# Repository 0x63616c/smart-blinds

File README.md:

# Smart Blinds

Compact, rechargeable blind controllers for seven windows, with one spare.
White printed enclosures, USB-C charging, physical buttons and Home Assistant control.

**Current stage: prototype design.** This repository is being designed afresh. The inherited
USB-C boards below are references, not the new blind controller or a battery charger.
No complete unit has been built or physically validated.

[Current enclosure](docs/mechanical/enclosure-v2.md) · [Enclosure comparison](docs/mechanical/2026-10-19-holder-and-drive-trade-study.md) · [Electronics comparison](docs/electrical/2026-10-19-power-control-trade.md) ·
[Design brief](docs/brief.md) · [Progress](docs/status.md) · [Measurements](docs/measurements.json) ·
[Validation plan](docs/verification-plan.md) · [Shopping list](bom/README.md) · [Wi-Fi motion checkpoint](docs/firmware/wifi-motion.md) · [Local ownership](docs/firmware/local-ownership.md)

## The product

- One integrated controller and one 3S2P Samsung 50E battery pack per blind.
- PCB-mounted cell holders are being evaluated on a separate protected carrier to simplify assembly.
- Existing Recfountik JGB37-520 12 V / 111 RPM encoder motors.
- A small white enclosure mounted low on the wall, with accessible USB-C and up/down buttons.
- Group commands align the **physical bottom edges** of different-height blinds.
- A short remote-command preparation delay is acceptable; immediate local response is the target. Raw button STOP/wake is implemented; calibrated up/down gestures are still being completed.
- 60 days between charges is the design target; 90 days is a stretch, pending measured power use.
- Compare at least three enclosure layouts before choosing the packaging and PCB outline.
- Optimize the total cost for eight units, including JLCPCB assembly fees, packs, fixings and wiring.

The first milestone is a complete, costed design for **two prototypes**. Two different-height
blinds are needed to test synchronization before committing to the eight-unit batch.

## Design gallery

**Cleaner layout in progress:** the [54 × 80 mm controller](hw/routing/clean-main/)
is rebuilt from the current circuit source, with local footprints and all referenced models.
It has 206 gridded components, outward-facing connectors, rounded corners and sparse markings.
The [current review](docs/reviews/2026-10-21-clean-layout/source-driven-route.md)
records the geometry, library, ground-return and source checks.
**352 connections remain open**; this is a partial design, not a fabrication release.
The automatic gallery rebuilds the current route before rendering it. The smaller
196-part route is retained as a collapsed historical comparison.

These images are generated from the design sources. [Preview generation and provenance](docs/previews.md).
A green preview badge means the images generated successfully, not that the hardware is validated.
The [current 118 × 196 × 77 mm enclosure](docs/mechanical/enclosure-v2.md) has
an inward-facing controller, removable protected cassette and 22 installed
printed pieces. Its source-bound local review passes 17 nominal geometry checks;
physical motor/holder fit, strength and assembly remain untested. The current
assembly pictures use component envelopes; the KiCad view shows the populated board.
Older enclosure images retain their [known orientation error](docs/mechanical/pcb-orientation-review.md)
and are labelled historical. Fresh current-source images are published by CI.

<!-- previews:start -->
### Cleaner controller — current routing draft

Current 54 × 80 mm black four-layer controller draft, regenerated from the 206-part circuit capture. Grid placement, outward-facing connectors and the implemented USB-C, local supply and protection routes are checked on the saved filled board. 352 connections and three documented hybrid-footprint type findings remain; current, thermal, surge, RF and physical qualification are unfinished. Not a fabrication release.

[Source](hw/routing/clean-main/emit.py) · [Generated files](docs/generated/clean-controller-route/)

<details>
<summary>Historical enclosure — current exterior</summary>

Historical assembly checkpoint. Its PCB orientation and service geometry are superseded by the ongoing enclosure rework. 115 × 174 × 71 mm white enclosure candidate, with front buttons and underside USB-C. Buttons project to 72.2 mm. This compact version requires holder tails and solder joints trimmed to the documented limit; motor-family fit and printed tolerances remain provisional.

[Source](cad/source/compact_retained.scad) · [Generated files](docs/generated/compact-holder-closed/)

</details>

<details>
<summary>Historical removable battery cassette and compact drive</summary>

Historical assembly checkpoint. Its PCB orientation and service geometry are superseded by the ongoing enclosure rework. Two opposing three-cell carrier boards fit in a removable cassette. Separate controller supports, cable routes and adjustable front buttons are modeled. The controller is shown as a reserved volume; exact holder fastening and physical load tests remain open.

[Source](cad/source/compact_retained.scad) · [Generated files](docs/generated/compact-holder-assembly/)

</details>

<details>
<summary>Historical enclosure — service view</summary>

Historical assembly checkpoint. Its PCB orientation and service geometry are superseded by the ongoing enclosure rework. The cover and cassette lid are separated to show access. Two integral cleats and one mounting screw retain the cassette; its modeled release and removal paths clear the controller and drive. These are prototype-fit files, pending tolerance and load qualification.

[Source](cad/source/compact_retained.scad) · [Generated files](docs/generated/compact-holder-exploded/)

</details>

<details>
<summary>Current controller — source placement</summary>

Current 54 × 80 mm unrouted source capture: 206 components and 649 physical pin identities. The routing emitter applies three reviewed protection-part moves and the per-part model/silkscreen refinements. The larger routed draft appears above.

[Source](hw/layouts/blind-main/main-test/main-test.kicad_pcb) · [Generated files](docs/generated/main-controller-placement/)

</details>

<details>
<summary>Historical smaller controller — partial power routing</summary>

Historical 196-part, 54 × 68.5 mm route retained for comparison. Its 1013 segments, 255 vias and 122 open connections belong to the earlier circuit and placement. It is not the current controller or a fabrication release.

[Source](hw/routing/blind-main/main-routed.kicad_pcb) · [Generated files](docs/generated/main-power-route/)

</details>

<details>
<summary>Companion battery carrier — experimental copper</summary>

Two-layer companion carrier with 35 copper segments, 12 vias and no disconnected nets. Silkscreen and library comparisons pass; four mounting-hole courtyard findings remain. Experimental only: current capacity, holder loading, insulation and pack assembly still require qualification.

[Source](hw/routing/blind-pack-companion/companion-routed.kicad_pcb) · [Generated files](docs/generated/companion-routed/)

</details>

<details>
<summary>Primary battery carrier — connected routing study</summary>

Experimental 451-segment, 129-via route with all 35 nets physically connected and zero unconnected items. Eleven injected-fault checks cover current/Kelvin topology, protected-ground communication clamps and same-net solder-land clearance. Silkscreen and library comparisons pass. Four mounting-hole courtyard findings and thermal, transient, holder and assembly qualification remain. Not a fabrication release.

[Source](hw/routing/blind-pack-primary/primary-routed.kicad_pcb) · [Generated files](docs/generated/primary-current-route/)

</details>

<details>
<summary>Reusable battery-loading fixture</summary>

Reusable workshop supports for the wired carrier pair. The rear tray is fitted before turning the cassette; broad captive pads and temporary clamps support the modeled sequence. Eight printed tools are shared across all builds and add no installed parts. Cell retention, handling forces and pigtail restraint still require physical qualification.

[Source](cad/source/holder_pair_fixture.scad) · [Generated files](docs/generated/holder-pair-fixture/)

</details>

<details>
<summary>Battery loading with the rear tray fitted</summary>

The first cell row is enclosed by the rear tray before turning onto a supporting cradle to load the second row. Two temporary clamps use broad pads against the tray. This is a nominal geometric sequence, pending load and tolerance tests.

[Source](cad/source/holder_pair_fixture.scad) · [Generated files](docs/generated/holder-pair-tray/)

</details>

<details>
<summary>Captive pressure pad detail</summary>

A broad captive pad spreads the temporary clamp load; the screw tip remains clear of the tray in the nominal model. Retention and head-stop geometry are checked. Safe tightening force and print creep remain unqualified.

[Source](cad/source/holder_pair_fixture.scad) · [Generated files](docs/generated/holder-pair-pad/)

</details>

<details>
<summary>Complete controller schematic</summary>

Eleven native KiCad sheets cover all 206 circuit features and 649 physical pin identities. The exported net partition matches the current capture; seven documented ERC findings remain. No physical hardware has been powered.

[Source](hw/schematics/blind-main/smart-blinds-main.kicad_sch) · [Generated files](docs/generated/main-controller-schematic/) · [PDF](docs/generated/main-controller-schematic/schematic.pdf)

</details>

<details>
<summary>Historical enclosure — mechanism section</summary>

Historical assembly checkpoint. Its PCB orientation and service geometry are superseded by the ongoing enclosure rework. Two captive M2 adjusters set the plungers to first electrical closure at the 0.4 mm positive stop. Jam nuts lock the setting. Switch return, printed friction, adjustment and repeated operation still require physical tests.

[Source](cad/source/compact_retained.scad) · [Generated files](docs/generated/compact-holder-buttons/)

</details>

<details>
<summary>Historical enclosure — removable assembly</summary>

Historical assembly checkpoint. Its PCB orientation and service geometry are superseded by the ongoing enclosure rework. Six holders on opposing carrier boards, a separate insulating barrier and a removable printed shell. The assembled cassette releases with a 2.5 mm lift and then moves forward; disconnect and handle the cables separately.

[Source](cad/source/compact_retained.scad) · [Generated files](docs/generated/retained-cassette/)

</details>

<details>
<summary>Historical enclosure — cutaway</summary>

Historical assembly checkpoint. Its PCB orientation and service geometry are superseded by the ongoing enclosure rework. The cassette pocket captures the integral backplate cleat. Nominal interference confirms capture before the release slide; printed strength, creep and fit remain prototype tests.

[Source](cad/source/compact_retained.scad) · [Generated files](docs/generated/retained-cleat-section/)

</details>

<details>
<summary>Holder carrier enclosure — provisional exterior</summary>

Original 170 × 158 × 64 mm packaging study using six PCB-mounted holders and an independent chain shaft. Retention, electrical layout and purchased-part fit are still in development.

[Source](cad/source/packaging_v2.scad) · [Generated files](docs/generated/holder-closed/)

</details>

<details>
<summary>Battery holders and supported drives, at the same scale</summary>

Six packaging reservations. The two welded-pack options remain size references; the holder alternatives compare assembly effort, width and depth.

[Source](cad/parameters/packaging-v2.json) · [Generated files](docs/generated/holder-comparison/)

</details>

<details>
<summary>Protected carrier and supported drive — exploded study</summary>

Original 170 × 158 × 64 mm packaging study using six PCB-mounted holders and an independent chain shaft. Retention, electrical layout and purchased-part fit are still in development.

[Source](cad/source/packaging_v2.scad) · [Generated files](docs/generated/holder-exploded/)

</details>

<details>
<summary>One protected carrier — internal arrangement</summary>

Original 170 × 158 × 64 mm packaging study using six PCB-mounted holders and an independent chain shaft. Retention, electrical layout and purchased-part fit are still in development.

[Source](cad/source/packaging_v2.scad) · [Generated files](docs/generated/holder-inside/)

</details>

<details>
<summary>Motor driver — native KiCad circuit study</summary>

Fourteen components and 43 physical pin connections agree with the atopile board graph. This open block has four documented ERC boundary findings; supply, controller, motor connector and regenerative-energy clamp are not yet integrated.

[Source](hw/schematics/blind-controller/motor-test.kicad_sch) · [Generated files](docs/generated/motor-schematic/)

</details>

<details>
<summary>Motor cutoff and reset — native KiCad circuit study</summary>

Four ICs and ten passive parts. All 49 physical pin connections checked against the compiled circuit; two explicit external-power ERC findings. Physical cutoff and full-board qualification remain open.

[Source](hw/schematics/blind-supervisor/supervisor-test.kicad_sch) · [Generated files](docs/generated/supervisor-schematic/)

</details>

<details>
<summary>USB-C-fed 3S charger — native KiCad circuit study</summary>

36-part capture with 101 physical pins checked. A fourth PMID capacitor follows DC-bias review; effective capacitance remains a curve-based planning estimate. Ten explicit ERC findings and unfinished power/pack integration. Not a charging or fabrication release.

[Source](hw/schematics/blind-charger/charger-test.kicad_sch) · [Generated files](docs/generated/charger-schematic/)

</details>

<details>
<summary>Regenerative clamp and thermal latch — native KiCad circuit study</summary>

38 parts and 105 physical pins checked. Two explicit external-power ERC findings. Pulse energy, response time, thermal coupling and sustained back-drive remain unqualified.

[Source](hw/schematics/blind-regen/regen-test.kicad_sch) · [Generated files](docs/generated/regen-schematic/)

</details>

<details>
<summary>3.3 V logic supply — native KiCad circuit study</summary>

12 parts and 31 physical pins checked. Internal 3.3 V divider; 1 A design envelope. Two external-power ERC findings. Biased capacitance, load transients, layout and hardware qualification remain open.

[Source](hw/schematics/blind-regulator/regulator-test.kicad_sch) · [Generated files](docs/generated/regulator-schematic/)

</details>

<details>
<summary>Protected 3S2P carrier — native KiCad circuit study</summary>

33 parts and 103 physical pins checked, including three-cell sensing and six branch fuses. Fifteen explicit ERC boundary findings. Holder, thermistor, connector and secondary protection integration remain open; no battery fault safety or fabrication approval is implied.

[Source](hw/schematics/blind-carrier/carrier-test.kicad_sch) · [Generated files](docs/generated/carrier-schematic/)

</details>

<details>
<summary>USB-C PD input — native KiCad circuit study</summary>

33 parts and 113 physical pins checked. Three explicit external-power ERC findings. Mandatory factory PD profile, surge behavior, startup and integrated charging remain unqualified; not a fabrication release.

[Source](hw/schematics/blind-usb/usb-test.kicad_sch) · [Generated files](docs/generated/usb-schematic/)

</details>

<details>
<summary>Compact enclosure — provisional exterior</summary>

Earlier study, before PCB-mounted holders and independent shaft support. Initial compact direct-drive packaging candidate. Original parametric geometry; purchased-part fit and the holder-carrier alternative remain under review.

[Source](cad/source/smart_blinds.scad) · [Generated files](docs/generated/compact-closed/)

</details>

<details>
<summary>Four layouts at the same scale</summary>

Earlier study, before PCB-mounted holders and independent shaft support. Calculated front footprints from the original packaging study. Dimensions and purchased-part envelopes remain provisional.

[Source](cad/parameters/packaging.json) · [Generated files](docs/generated/packaging-comparison/)

</details>

<details>
<summary>Compact enclosure — exploded study</summary>

Earlier study, before PCB-mounted holders and independent shaft support. Enclosure and internal fit study. Motor, cells and PCB are reserved envelopes; attachment and drive details are still being developed.

[Source](cad/source/smart_blinds.scad) · [Generated files](docs/generated/compact-exploded/)

</details>

<details>
<summary>Compact direct drive — packaging study</summary>

Earlier study, before PCB-mounted holders and independent shaft support. Compact direct drive with three cell columns and two depth layers. Provisional packaging study.

[Source](cad/source/smart_blinds.scad) · [Generated files](docs/generated/compact-assembly/)

</details>

<details>
<summary>Wide and shallow — packaging study</summary>

Earlier study, before PCB-mounted holders and independent shaft support. Six cells across one depth layer. Provisional packaging study.

[Source](cad/source/smart_blinds.scad) · [Generated files](docs/generated/broad-assembly/)

</details>

<details>
<summary>Narrow with right-angle drive — packaging study</summary>

Earlier study, before PCB-mounted holders and independent shaft support. Narrow footprint with a right-angle transmission envelope. Gears are not yet functional designs.

[Source](cad/source/smart_blinds.scad) · [Generated files](docs/generated/narrow-assembly/)

</details>

<details>
<summary>Tall and shallow direct drive — packaging study</summary>

Earlier study, before PCB-mounted holders and independent shaft support. Two vertical rows of three cells in a single depth layer. Provisional packaging study.

[Source](cad/source/smart_blinds.scad) · [Generated files](docs/generated/slim-assembly/)

</details>

<details>
<summary>Battery life and wake-up cost</summary>

Source-generated energy scenarios, not measured runtime. Motor-branch current and awake logic are counted separately. Additional service wake time replaces idle; use zero if already included in a measured idle average.

[Source](hw/sim/blind-control/plot_energy.py) · [Generated files](docs/generated/battery-energy/)

</details>

<details>
<summary>PD12V6Mini — inherited power-board reference</summary>

Existing e8s USB-C PD to 12.6 V power supply. This is not the new controller or a battery charger; no new hardware validation is implied.

[Source](hw/layouts/pd12v6mini/pd12v6mini.kicad_pcb) · [Generated files](docs/generated/pd12v6mini-reference/)

</details>

<!-- previews:end -->

The enclosure views show original packaging studies with provisional motor and PCB envelopes.
The fresh integrated controller is still being designed; the inherited board is labelled separately.

## What's in the project

| Folder | Contents |
|---|---|
| `cad/` | Original packaging studies, enclosure sources and print/export instructions |
| `hw/` | Board sources, KiCad layouts, parts and simulation models |
| `firmware/` | Embedded control, calibration, safety state machine and tests |
| `integrations/` | Home Assistant coordination and integration as implemented |
| `bom/` | Per-unit, two-prototype and eight-unit cost/inventory records |
| `docs/` | Requirements, evidence, design comparisons and validation results |
| `tools/` | Reproducible documentation and preview generation |

## Development

The inherited electrical project uses atopile and KiCad 10. See [hardware instructions](hw/README.md).
The documentation renderer uses Python 3.11+ and KiCad 10; it reads layouts without regenerating them.

```sh
python3 tools/render_previews.py
```

CI renders registered sources on changes, uploads review artifacts for pull requests, and refreshes
committed previews on `main`. Source hashes and tool versions accompany the images. Print and
manufacturing releases must also pass the separate [validation gates](docs/verification-plan.md).

## Provenance

Created from private [e8s](https://github.com/0x63616c/e8s) at
`3ad0a29efcf933d6b887825998ced19d0c5ab11e`, preserving its history and working reference boards.
The original e8s repository is unchanged. Older Smart Shades, Smart Blinds and Packmule projects
are evidence sources only: [archive findings](docs/research/archive-findings.md).
Their architecture and completion claims do not carry forward into this design.

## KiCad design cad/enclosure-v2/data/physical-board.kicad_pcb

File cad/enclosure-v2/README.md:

# Current enclosure candidate

118 × 196 × 77 mm case with an inward-facing 54 × 80 mm controller, protected
battery cassette and integral front buttons. This is prototype geometry;
physical fit and electrical qualification remain open.

[Inventory](inventory.md) · [Print list](print-list.csv) · [Service sequence](service.md) ·
[Parameter and mesh limits](dependencies.md) · [Reviewed handoff](handoff.md)

The imported local checkpoint passed 17 geometry checks against native board
`03a6b3dc…`: 206 footprints and 120 rear vias. It preserves four original
cassette-overlap witnesses. Only the front and rear cassette shapes changed;
the other 28 export roles retain their prior geometry. There are 22 installed
pieces per blind, plus two optional cosmetic plugs and a shared button nest.
The older holder-loading fixture has not been requalified for this revision.

CI first compares its newly built native PCB with this package's explicit board
and source bindings. A changed board must be deliberately reviewed and rebound;
the copied old board cannot silently approve a newer route.

Use Python with `numpy==2.3.5`, `manifold3d==3.3.2` and OpenSCAD on the path:

```sh
python cad/enclosure-v2/rebuild.py
```

This sequentially checks parameters, exports parts, runs all 17 checks, computes
the inventory and renders four local cutaways. Linux needs Xvfb for rendering.
The central preview workflow separately renders closed, cover-off and service
views from `source/assembly_v2.scad`. Those views use envelopes for prominent
PCB parts; the native KiCad view shows the populated controller.

`evidence/reviewed-checkpoint.json` preserves the original local review's file
hashes. `evidence/promotion-delta.json` records subsequent integration edits,
including the black board display color. Fresh CI reports are new evidence;
they do not restamp that human review. `freeze.py` is an explicit one-time
review operation and is excluded from the ordinary rebuild.

Two exact inherited cassette meshes remain Boolean source operands. The
cassette is not arbitrarily resizable. Motor/holder fit, insulation, print
strength and creep, wire bending, catch release and loaded handling still need
physical tests. The optional home-sensor path remains unfinished. No purchase
or fabrication is authorized by a geometry pass.

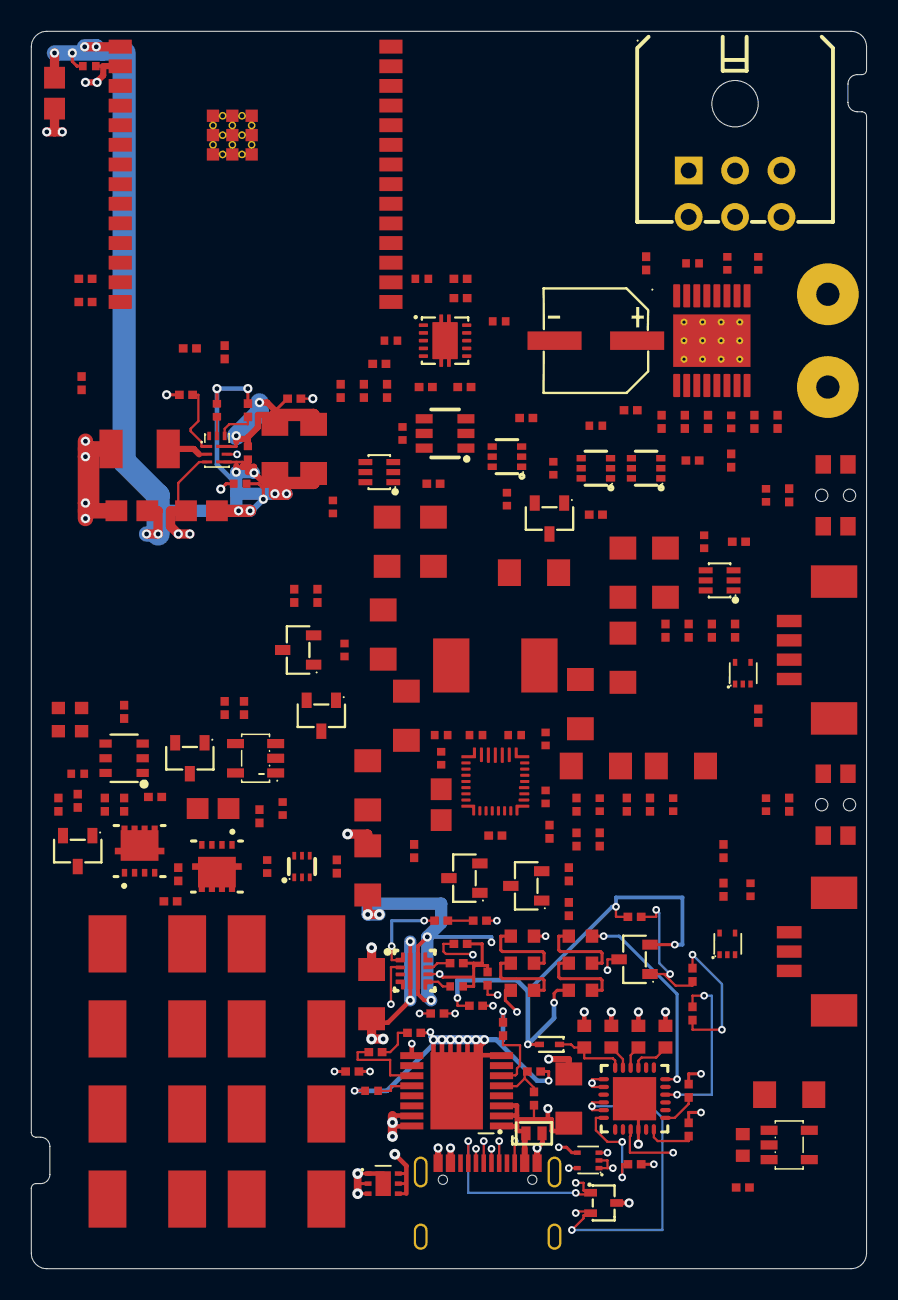
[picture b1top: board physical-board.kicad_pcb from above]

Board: 4 copper layers, 54.0 x 80.0 mm, 206 parts (0 on the bottom side), 117 nets.

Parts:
C1, C2, C6, C7, C9, C10, C11, C12, C16, C17, C18, C19, C20, C40, C42: V_3a95dcb1ea8f0c6a36c4
C3, C4, C5, C15, C46, C50, C62: V_38dae221a2b2f2799770
C8, C13, C21, C22, C23, C24, C26, C27, C28, C29, C30, C33, C34, C35, C36, C37, C38, C41, C45, C52, C55, C56, C57, C58, C60: V_f82fdad5f87db4b863ca
C14, C25, C39, C43, C44: V_6223558e7588d04b48f2
C31: V_b8d5b98c2ce33484bb6b
C32: V_645b23f54fc7d7d42102
C47, C48, C51, C53, C61: V_f6bd1233a6f74738242e
C49, C54, C63: V_d10f4007b7d33b8aec73
C59: V_b8aee312a809c0941dd1
D1, D6: V_a3e351692d4e59c49859
D2: V_39b923155ed4e4f18b4e
D3: V_3da48fb411b80eb065b8
D4: V_89760a47a5abe975142f
D5: V_cac1c9e608288319f3d7
J1: V_62aca2d77678f6ab5469
J2: V_71e31e344584da49c4c3
J3: V_e930507233e0ef941fdf
L1: V_18f7cb8d0dfbe41749e8
L2: V_39175f581dc0c1684b79
Q1, Q2, Q3, Q8: V_00e364f508d61cf8565d
Q4, Q5, Q7, Q10: V_31bce82ae1eef8cfc1c8
Q6: V_ed852e2b4fef5200624c
Q9: V_e7920e4bfadd3f79a25b
R1, R5, R8, R9, R10, R56: V_214b505d65ee126c9595
R2, R3, R4, R6, R7, R13, R18, R19, R20, R22, R24, R26, R29, R30, R32, R33, R34, R35, R36, R37, R38, R44, R46, R49, R50, R57, R62, R63, R66, R79, R80, R83, R85, R87, R89, R90, R92, R93, R96: V_bf5238dc572db944eb6c
R11, R12, R14, R15, R16, R17, R21, R23, R25, R27, R28, R39, R40, R41, R47, R48, R51, R65, R67, R68, R77, R78, R81, R82, R88, R91, R97, R98: V_f56cc3dad7ad25e121bb
R31: V_3eeed1989cba6701ce17
R42, R43, R69, R70, R71, R72, R73, R74: V_45a6fa73a533bb5372ab
R45, R58: V_649d45776ca84f9028d2
R52: V_b7015519213b516f949b
R53, R54, R55, R59, R60, R61: V_41980b6d0df9c47a0426
R64: V_e2400a0ced35f25a9f41
R75, R76: V_ff3bc35531d56c5fd365
R84, R86: V_a0e9f8de16dcd862e89e
R94: V_1f008dcd3ec8e03d520a
R95: V_27a220b792d3f0e0f665
SW1, SW2: V_0d044bddac0edce015d0
TP1, TP2: V_6019801a2825a4a5a71d
U1: V_685768986c16e1883cf0
U2, U14: V_623cdc0641dcc2ec8d8d
U3: V_234cf592a56e0c328a3f
U4: V_5809bf28ef8586c5bd0d
U5: V_bf0a0eaed5612a98827e
U6: V_f83e8ad16839a825ee6b
U7: V_2cc89b9d481f6da46d83
U8, U12, U17: V_d4d91a411e82c9fc3e61
U9: V_1f780da4969e56ef0365
U10: V_b77ef15890283ded3618
U11: V_a5b716336ce0a6341a90
U13: V_d63ebd48523dce10781d
U15: V_8c4e4e29290d57f42fde
U16: V_74ea8f6ec7ad66b03116
U18: V_55a9fc332bb062f749b2
U19: V_c7b0c9009cc7fdd63a10
USBC1: V_f32cb9c1c37a467aa1f1

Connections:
1: C4.1, U1.4
2: C5.2, L1.2, U1.26
4: U2.4, U3.7
6: U2.6, U3.6
10: R29.2, U3.10
ALERT: R63.2, U1.21, U3.24, U11.19
BATP: C3.1, R1.2, U1.18
C: Q3.3, R66.1
CC2: D4.2, U11.4, U11.5, USBC1.B5
CE_n: Q1.3, R2.2, U1.13
CPH: C32.1, U4.13
CPL: C32.2, U4.14
CWD: C59.1, U16.2
D: Q10.3, R32.2, U3.19, U4.4
DISCH: R55.2, U11.9
DVDT: C62.1, U18.12
EN: R68.1, U12.4, U13.3
G: Q4.1, Q7.1, Q8.3, Q10.1, R88.1
ILIM: R64.1, U18.11
ILIM_HIZ: R4.1, R5.2, U1.17
ILM: R52.1, U10.9
MODE: R94.1, U18.6
MODE_S_CONF: R45.1, U9.7
MR: R93.2, U15.3, U16.8
OUTB: R40.1, U5.6
OVP: R95.1, R96.2, U18.5
PG: R46.2, U9.1
PMODE: R35.2, U4.16
PROG: R8.1, U1.20
RESET: R62.1, U11.6
SCL: J1.4, R27.2, U1.14, U3.12, U11.7
SDA: J1.3, R28.2, U1.15, U3.11, U11.8
SDRV: C15.1, U1.24
SS_TR: C46.1, U9.8
SW: L2.1, U9.2
VBUS_EN_SNK: R50.2, U11.16
VBUS_VS_DISCH: R61.2, U11.18
VCP: C33.1, U4.12
WDI: U14.4, U16.7
Y: R38.1, R39.1, U4.3, U17.4
allow_n-line: R24.2, U3.21, U12.6
boot_n: R19.2, U3.15
c_1v2-1: C47.1, U11.21
c_2v7-1: C48.1, U11.23
c_adc-1: C24.1, R14.2, R15.1, U3.27
c_boot1-1: C4.2, L1.1, U1.28
c_boot2-1: C5.1, U1.19
c_down-1: C27.1, R22.2, SW1.1, SW1.2, U3.9
c_hot_filter-1: C37.1, C39.1, C55.1, Q8.2, R80.1, R81.1, R83.1, U6.5, U7.1, U7.4, U7.5, U7.6
c_pmid1-1: C9.1, C10.1, C11.1, C12.1, C13.1, U1.29
c_ref-1: C34.1, R36.2, R37.1, U4.5
c_regn-1: C14.1, R2.1, R5.1, R10.1, U1.5
c_up-1: C30.1, R30.2, SW2.1, SW2.2, U3.8
c_vdd-1: C51.1, D3.1, U11.24
channel_a: D1.3, J2.3, R12.1, R13.2
channel_b: D1.5, J2.4, R17.1, R18.2
charger-1: Q1.1, Q2.3, R3.1
charger-1-1: Q2.1, R6.2, R7.1
connector-1: D4.1, U11.1, U11.2, USBC1.A5
controller-1: R11.1, R12.2, U2.1
controller-1-1: R16.1, R17.2, U2.3
controller-1-2: R21.1, U3.13
controller-1-3: R23.1, U3.14
controller-2: C29.1, R25.2, R26.2, U3.26
current_raw: R14.1, R31.1, U4.6
efuse-1: R65.1, R67.2, U10.1
encoder-output-hv: C54.1, J2.2, R13.1, R18.1, U13.5
guarded-hv: C63.1, D3.2, Q3.2, R51.1, R57.1, R59.1, R97.1, U10.5, U18.15, U18.16, U19.4, U19.5, U19.6
heartbeat-line: R92.2, U3.25, U14.3
home_contact_n: D6.3, D6.5, J3.3, R25.1
host_logic-hv: C23.1, C25.1, C26.1, C28.1, C43.1, C44.1, C45.1, C52.1, C56.1, C57.1, C58.1, C60.1, C61.1, L2.2, Q2.2, R7.2, R19.1, R20.1, R22.1, R24.1, R26.1, R27.1, R28.1, R29.1, R30.1, R32.1, R35.1, R36.1, R46.1, R63.1, R89.1, R90.1, R92.1, R93.1, U2.5, U3.2, U8.5, U9.3, U11.22, U12.5, U14.5, U15.5, U15.6, U16.1, U16.10, U17.5
hv: C1.1, C2.1, C31.1, C33.2, C35.1, C36.1, C38.1, J1.1, Q5.2, R1.1, R41.1, R42.1, R69.1, R71.1, R73.1, R84.1, R86.1, U1.22, U1.23, U4.11, U5.5, U6.1
in1-1: R33.1, U3.16, U4.1
in2-line: R34.1, U3.17, U4.2
line: R6.1, R20.2, U3.20
logic_supply-EN: R44.2, U9.5
lv: C1.2, C2.2, C3.2, C6.2, C7.2, C8.2, C9.2, C10.2, C11.2, C12.2, C13.2, C14.2, C15.2, C16.2, C17.2, C18.2, C19.2, C20.2, C21.2, C22.2, C23.2, C24.2, C25.2, C26.2, C27.2, C28.2, C29.2, C30.2, C31.2, C34.2, C35.2, C36.2, C38.2, C39.2, C40.2, C41.2, C42.2, C43.2, C44.2, C45.2, C46.2, C47.2, C48.2, C49.2, C50.2, C51.2, C52.2, C53.2, C54.2, C55.2, C56.2, C57.2, C58.2, C59.2, C60.2, C61.2, C63.2, D1.1, D1.2, D1.4, D2.1, D2.2, D2.4, D4.3, D5.2, D6.1, D6.2, D6.4, J1.2, J1.6, J2.1, J3.1, Q1.2, Q4.2, Q7.2, Q9.1, Q9.2, Q9.3, Q10.2, R3.2, R4.2, R8.2, R9.2, R11.2, R15.2, R16.2, R31.2, R33.2, R34.2, R37.2, R38.2, R39.2, R45.2, R47.2, R48.2, R52.2, R56.2, R62.2, R65.2, R68.2, R77.2, R78.2, R81.2, R82.2, R85.2, R88.2, R91.2, R97.2, SW1.3, SW1.4, SW2.3, SW2.4, U1.10, U1.11, U1.27, U2.2, U3.1, U3.28, U3.29, U3.30, U3.31, U3.32, U3.33, U3.34, U3.35, U3.36, U3.37, U4.9, U4.15, U4.17, U5.2, U5.3, U6.2, U7.2, U8.2, U8.3, U9.4, U10.8, U11.10, U11.25, U12.2, U12.3, U13.2, U14.2, U15.2, U16.5, U16.6, U16.11, U17.1, U17.2, U18.9, U19.1, U19.2, U19.3, U19.7, USBC1.1, USBC1.2, USBC1.3, USBC1.4, USBC1.A1B12, USBC1.B1A12
motor_a: TP1.1, U4.8
motor_b: TP2.1, U4.10
motor_request_n-line: R89.2, U3.18, U14.1
motor_sleep_n-Y: R91.1, U8.4, U17.3
pack_ntc: C22.1, J1.5, R9.1, R10.2, U1.16
pd-1: R47.1, U11.12
pd-1-1: R48.1, U11.13
q_drive-1: Q5.3, Q6.4, R75.1, R77.1, R78.1
q_enable-1: Q3.1, R49.1, R51.2
r_base1-1: R49.2, R50.1
r_cutoff_limit-1: R64.2, R98.1
r_dump1a-1: R42.2, R43.1
r_dump2a-1: R69.2, R70.1
r_dump3a-1: R71.2, R72.1
r_dump4a-1: R73.2, R74.1
r_feedback1-1: R75.2, R76.1
r_out_dis1-1: R53.2, R54.1
r_out_dis2-1: R54.2, R55.1
r_ov_top1-1: R57.2, R58.1
r_raw_dis1-1: R59.2, R60.1
r_raw_dis2-1: R60.2, R61.1
r_threshold_top1-1: R86.2, R87.1
r_uv_top1-1: R66.2, R67.1
raw-hv: C49.1, D5.1, R96.1, U18.1, U18.2, U18.3, USBC1.A4B9, USBC1.B4A9
regen-2: C37.2, Q8.1, R79.2, R80.2
regen-2-1: Q6.5, Q6.6, Q6.7, Q6.8, Q6.9, R43.2, R70.2, R72.2, R74.2
regen-2-2: Q5.1, R40.2, R41.2
reset_n: R90.2, U3.3, U8.1, U12.1, U15.1
series_mid: Q6.1, Q6.2, Q6.3, Q9.5, Q9.6, Q9.7, Q9.8, Q9.9
source-hv: C16.1, C17.1, C18.1, C19.1, C20.1, C21.1, C40.1, C41.1, C42.1, C53.1, R44.1, U1.25, U9.6, U13.1
supervision-6: U8.6, U14.6, U16.3
thermal_gate: Q4.3, Q9.4, R82.1, R84.2
thermal_ok: Q7.3, R79.1, R83.2, U7.3, U17.6
threshold: R76.2, R85.1, R87.2, U5.4
usb-2: C62.2, R94.2, R95.2, R98.2, U18.8, U18.17
usb-2-1: R56.1, R58.2, U10.2
usb-DVDT: C50.1, U10.7
usb-output-hv: C6.1, C7.1, C8.1, R53.1, U1.2, U1.3, U1.8, U1.9, U10.6
usb_dm: D2.5, R21.2, USBC1.A7, USBC1.B7
usb_dp: D2.3, R23.2, USBC1.A6, USBC1.B6

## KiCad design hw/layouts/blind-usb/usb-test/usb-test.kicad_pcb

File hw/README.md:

# Hardware

**Inherited references:** PD12V6 and PD12V6Mini are USB-C power supplies. They are not complete
battery chargers or the new integrated smart-blind controller. See [the current brief](../docs/brief.md).

atopile project. One build target per board in `ato.yaml`.

- `boards/` — one `.ato` per board, each with an `App` module
- `parts/` — local part definitions (fetched with `scripts/fetch_part.py Cxxxx`, no atopile login)
- `layouts/<board>/` — KiCad layout for each board (committed)
- `layouts/<board>_manual/` — same placement, no tracks: the copy to route by hand (atopile allows one layout per folder)
- `scripts/` — placement/routing scripts and the review pipeline
- `datasheets/` — PDFs + text extracts used while designing
- `build/` — generated outputs (ignored)

## Workflow

```
uv run ato build -b pd12v6      # compile .ato -> netlist/BOM, sync layout
./scripts/review.sh             # build + place/route + DRC + images + STEP into build/review/
./scripts/review.sh --open      # ...and open the board in KiCad
```

Each board's layout is fully scripted (`scripts/layout_<board>.py` places, `routes_<board>.py` routes,
shared plumbing in `scripts/pcbkit.py`) and
idempotent: rerunning regenerates the same board, so edit the scripts rather than the .kicad_pcb.
`layout_<board>.py --place-only` writes the hand-route copy (`layouts/<board>_manual/`); it keeps
placement, zones, outline and silk and drops every track and via. The review script runs both.
Scripts run under KiCad's bundled Python (KiCad 10). Design notes: `../docs/pd12v6/design.md`, `../docs/pd12v6/mini.md`.

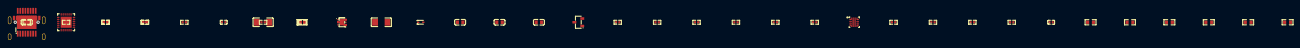
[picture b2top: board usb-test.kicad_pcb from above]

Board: 2 copper layers, 42 parts (0 on the bottom side), 37 nets, no tracks yet.

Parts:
C1, C2, C5, C6: C0603
C3, C8: C1206
C4, C7: C0402
D1: SOD-523_L1.2-W0.8-LS1.6-RD
D2: SOT-323-3_L2.1-W1.3-P1.32-LS2.1-BR
D3: DFN1610-2_L1.6-W1.0-P1.05-RD
Q1: SOT-23-3_L2.9-W1.3-P1.90-LS2.4-BR
R1, R2, R3, R4, R5, R6, R10, R11, R12, R16, R17, R18, R19, R20, R21, R22, R23, R24, R25: R0402
R7, R8, R9, R13, R14, R15: R0603
U1: VQFN-10_L2.0-W2.0-P0.45-TL
U2: QFN-24_L4.0-W4.0-P0.50-BL-EP2.8
U3: TPS26600_PWP16
U4: TVS1800_DRV6
USBC1: HRO_TYPE_C_31_M_12

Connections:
1: C1.1, U2.21
2: C7.2, R18.2, R22.2, R25.2, U3.8, U3.17
C: Q1.3, R20.1
CC2: D2.2, U2.4, U2.5, USBC1.B5
DISCH: R9.2, U2.9
DVDT: C7.1, U3.12
ILIM: R17.1, U3.11
ILM: R6.1, U1.9
MODE: R18.1, U3.6
OVP: R22.1, R23.2, U3.5
RESET: R16.1, U2.6
VBUS_EN_SNK: R4.2, U2.16
VBUS_VS_DISCH: R15.2, U2.18
guarded-hv: C8.1, D1.2, Q1.2, R5.1, R11.1, R13.1, R24.1, U1.5, U3.15, U3.16, U4.4, U4.5, U4.6
hv: C6.1, U2.22
lv: C1.2, C2.2, C3.2, C4.2, C5.2, C6.2, C8.2, D2.3, D3.2, R1.2, R2.2, R6.2, R10.2, R16.2, R19.2, R24.2, U1.8, U2.10, U2.25, U3.9, U4.1, U4.2, U4.3, U4.7, USBC1.1, USBC1.2, USBC1.3, USBC1.4, USBC1.A1B12, USBC1.B1A12
output-hv: R7.1, U1.6
raw-hv: C3.1, D3.1, R23.1, U3.1, U3.2, U3.3, USBC1.A4B9, USBC1.B4A9
usb-1: C2.1, U2.23
usb-1-1: C5.1, D1.1, U2.24
usb-1-2: D2.1, U2.1, U2.2, USBC1.A5
usb-1-3: R19.1, R21.2, U1.1
usb-1-4: R1.1, U2.12
usb-1-5: R2.1, U2.13
usb-1-6: Q1.1, R3.1, R5.2
usb-1-7: R3.2, R4.1
usb-1-8: R17.2, R25.1
usb-1-9: R7.2, R8.1
usb-1-10: R8.2, R9.1
usb-1-11: R11.2, R12.1
usb-1-12: R13.2, R14.1
usb-1-13: R14.2, R15.1
usb-1-14: R20.2, R21.1
usb-2: R10.1, R12.2, U1.2
usb-DVDT: C4.1, U1.7
usb_dn: USBC1.A7, USBC1.B7
usb_dp: USBC1.A6, USBC1.B6

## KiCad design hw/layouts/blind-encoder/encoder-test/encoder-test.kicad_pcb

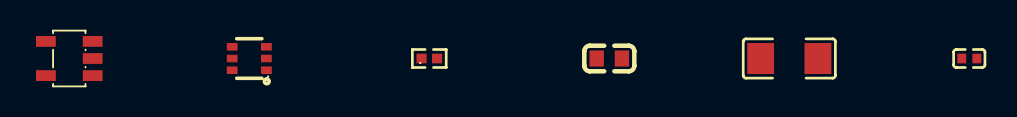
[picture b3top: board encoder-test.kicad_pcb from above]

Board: 2 copper layers, 6 parts (0 on the bottom side), 5 nets, no tracks yet.

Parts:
C1: C0402
C2: C0603
C3: C1206
R1: R0402
U1: SC-70-6_L2.0-W1.3-P0.65-LS2.1-BR
U2: SOT-23-5_L3.0-W1.7-P0.95-LS2.8-BR

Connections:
EN: R1.1, U1.4, U2.3
hv: C1.1, U1.5
lv: C1.2, C2.2, C3.2, R1.2, U1.2, U1.3, U2.2
output-hv: C3.1, U2.5
source-hv: C2.1, U2.1

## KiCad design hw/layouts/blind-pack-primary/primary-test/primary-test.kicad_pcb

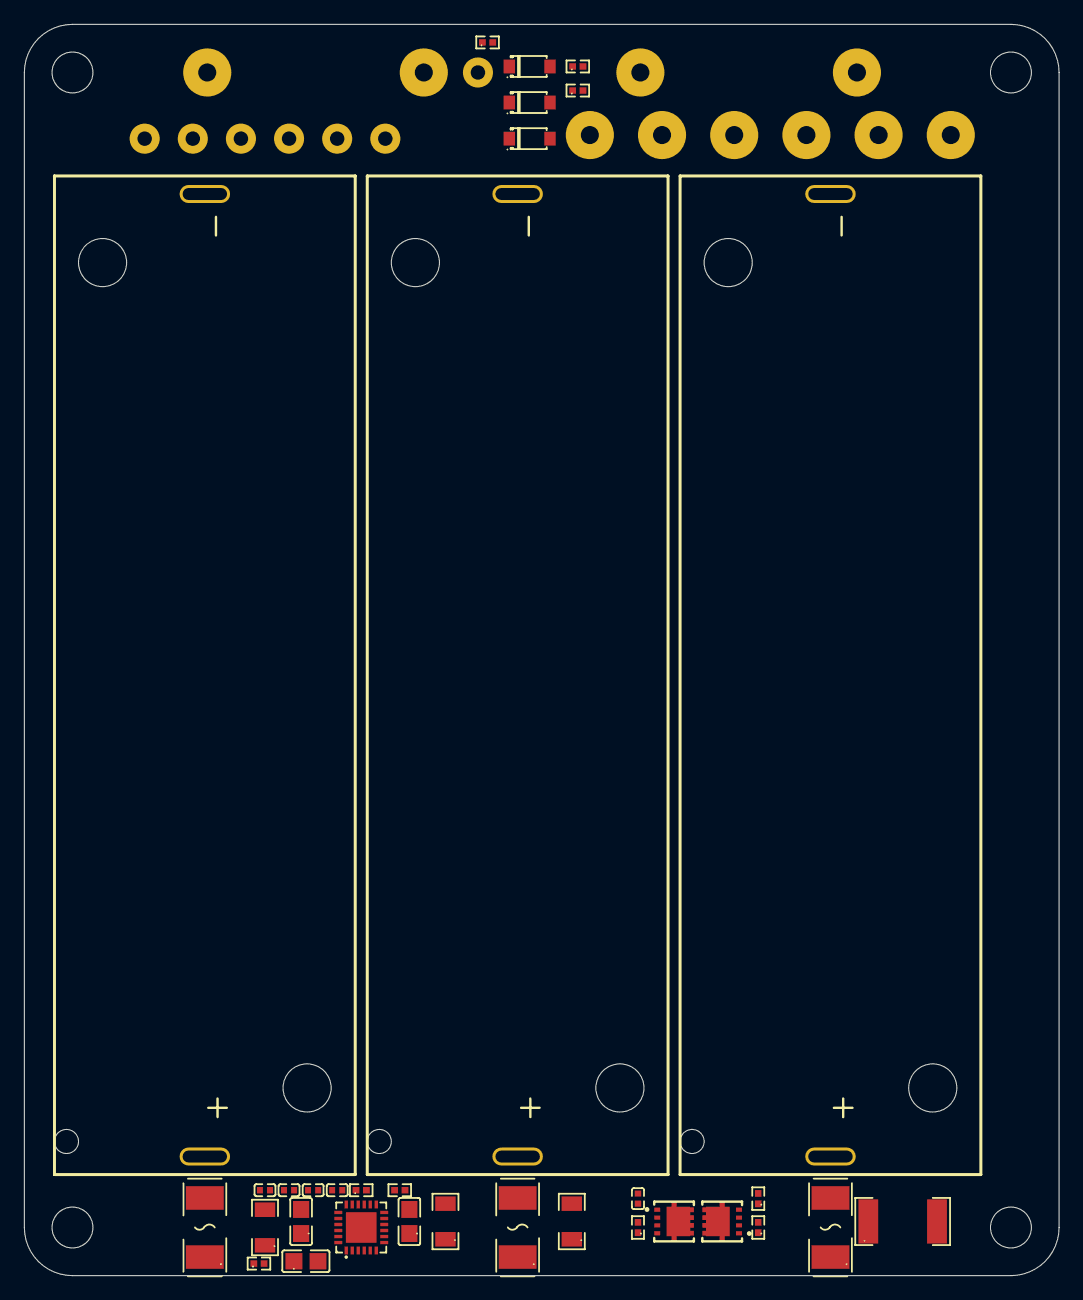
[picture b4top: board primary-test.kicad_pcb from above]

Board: 2 copper layers, 86.0 x 104.0 mm, 54 parts (0 on the bottom side), 34 nets, no tracks yet.

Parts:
BT1, BT2, BT3: BAT-TH_BH-21700-A5BJ001
C1, C2, C3, C4, C8: C0402
C5, C6, C7: C0805
D1, D2, D3: SOD-123_L2.8-W1.8-LS3.7-RD
F1, F2, F3: FUSE-SMD_L6.1-W2.7
H1, H2, H3, H4: M3 clearance 3.4 mm; MountingHole_M3_3.4mm
Q1, Q2: PDFN-8_L3.3-W3.3-P0.65-BL
R1, R2, R6, R7, R8, R9, R10, R11, R12: R0402
R3, R4, R5: R1206
R13: R2512
TP1, TP2, TP3, TP14, TP15, TP16, TP17: WirePadSignal
TP4, TP5, TP6, TP7, TP8, TP9, TP10, TP11, TP12, TP13: WirePad18
U1: QFN-24_L4.0-W4.0-P0.50-BL-EP2.6

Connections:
1: BT1.1, F1.1
2: C1.1, C2.2, R3.2, U1.21, U1.22
ALRT: R1.2, U1.7
AOLDO: R2.1, U1.12
BATTS: C3.1, R5.2, U1.24
CHG: R6.1, U1.3
CP: C5.1, U1.2
D: Q1.5, Q1.6, Q1.7, Q1.8, Q1.9, Q2.5, Q2.6, Q2.7, Q2.8, Q2.9
DIS: R7.1, U1.4
G: C4.1, Q1.4, R6.2
PCKP: R8.2, U1.6
PFAIL: R9.1, U1.11
SCL_DOD: R10.2, U1.8
SDA_DQ: R11.2, U1.9
carrier-1: BT2.1, F2.1
carrier-1-1: BT3.1, F3.1
carrier-1-2: D1.1, R1.1, TP3.1
carrier-1-3: D2.1, R10.1, TP6.1
carrier-1-4: D3.1, R11.1, TP7.1
carrier-contact: TP2.1, TP5.1
carrier-contact-1: BT1.2, C1.2, C6.2, C7.2, C8.2, R2.2, R9.2, R13.1, TP12.1, TP14.1, TP16.1, U1.15, U1.18, U1.19, U1.20, U1.25
carrier-contact-2: TP15.1, U1.10
carrier-contact-3: TP17.1, U1.16
carrier.protection-1: C5.2, C8.1, R12.2, U1.1
carrier.protection-1-1: C6.1, U1.17
carrier.protection-1-2: C7.1, U1.13
carrier.protection-2: C2.1, C3.2, R4.2, U1.23
carrier.protection-G: Q2.4, R7.2
contact: TP1.1, TP4.1
hv: Q2.1, Q2.2, Q2.3, R8.1, TP9.1
junction1: BT2.2, F1.2, R3.1, TP10.1
junction2: BT3.2, F2.2, R4.1, TP11.1
lv: D1.2, D2.2, D3.2, R13.2, TP8.1, U1.14
raw_top: C4.2, F3.2, Q1.1, Q1.2, Q1.3, R5.1, R12.1, TP13.1

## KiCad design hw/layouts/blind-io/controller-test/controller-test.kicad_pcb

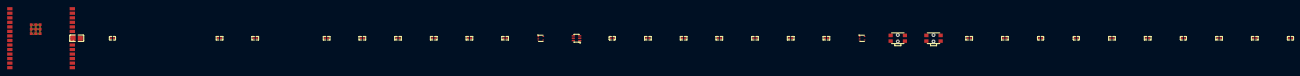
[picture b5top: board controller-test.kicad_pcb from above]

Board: 2 copper layers, 33 parts (0 on the bottom side), 23 nets, no tracks yet.

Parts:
C1, C3, C4, C5, C6, C8: C0402
C2: C0805
D1, D2: SOT-553-5_L1.6-W1.2-P0.50-LS1.6-TL-1
R1, R2, R3, R4, R5, R6, R7, R8, R9, R10, R11, R12, R13, R14, R15, R16, R19, R20, R21, R22: R0402
SW1, SW2: SW-SMD_4P-L3.5-W3.0-P1.6-LS4.6
U1: SOT-363_L2.0-W1.3-P0.65-LS2.1-BR
U2: WIRELM-SMD_ESP32-C6-WROOM-1

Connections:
1: C1.1, R4.2, R5.1, U2.27
2: C6.1, R15.2, R16.2, U2.26
4: U1.4, U2.7
6: U1.6, U2.6
10: R21.2, U2.10
11: R20.2, U2.11
12: R19.2, U2.12
boot_n: R9.2, U2.15
charge_allow_n-2: R10.2, U2.20
controller-1: C4.1, R12.2, SW1.1, SW1.2, U2.9
controller-1-1: C8.1, R22.2, SW2.1, SW2.2, U2.8
controller-1-2: R1.1, R2.2, U1.1
controller-1-3: R6.1, R7.2, U1.3
controller-1-4: R11.1, U2.13
controller-1-5: R13.1, U2.14
encoder_a_raw: D1.3, R2.1, R3.2
encoder_allow_n-2: R14.2, U2.21
encoder_b_raw: D1.5, R7.1, R8.2
encoder_rail-hv: R3.1, R8.1
hv: C2.1, C3.1, C5.1, R9.1, R10.1, R12.1, R14.1, R16.1, R19.1, R20.1, R21.1, R22.1, U1.5, U2.2
lv: C1.2, C2.2, C3.2, C4.2, C5.2, C6.2, C8.2, D1.1, D1.2, D1.4, D2.1, D2.2, D2.4, R1.2, R5.2, R6.2, SW1.3, SW1.4, SW2.3, SW2.4, U1.2, U2.1, U2.28, U2.29, U2.30, U2.31, U2.32, U2.33, U2.34, U2.35, U2.36, U2.37
usb_dm: D2.5, R11.2
usb_dp: D2.3, R13.2

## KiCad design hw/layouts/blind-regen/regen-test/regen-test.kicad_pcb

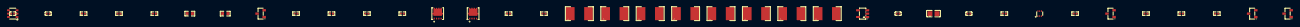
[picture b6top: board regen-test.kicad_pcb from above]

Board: 2 copper layers, 38 parts (0 on the bottom side), 19 nets, no tracks yet.

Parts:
C1, C2, C4, C5: C0402
C3: C0805
Q1, Q2, Q4, Q5: SOT-23-3_L2.9-W1.3-P1.90-LS2.4-BR
Q3, Q6: PDFN-8_L3.3-W3.3-P0.65-BL
R1, R2, R13, R14, R15, R16, R17, R18, R19, R20, R21, R22, R23, R24: R0402
R3, R4, R5, R6, R7, R8, R9, R10: R2512
R11, R12: R0603
U1: TSOT-23-6_L2.9-W1.6-P0.95-LS2.8-BR
U2: SOT-23-5_L3.0-W1.7-P0.95-LS2.8-BR
U3: SOT-5X3-6_W1.6-L1.2-P0.50-LS1.6-BL

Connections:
1: C3.1, C4.1, C5.1, Q5.2, R16.1, R17.1, R19.1, U2.5, U3.1, U3.4, U3.5, U3.6
2: C5.2, Q5.1, R15.2, R16.2
G: Q1.1, Q4.1, Q5.3, R24.1
OUTB: R1.1, U1.6
hv: C1.1, C2.1, Q2.2, R2.1, R3.1, R5.1, R7.1, R9.1, R20.1, R22.1, U1.5, U2.1
lv: C1.2, C2.2, C3.2, C4.2, Q1.2, Q4.2, Q6.1, Q6.2, Q6.3, R13.2, R14.2, R17.2, R18.2, R21.2, R24.2, U1.2, U1.3, U2.2, U3.2
regen-1: Q2.3, Q3.4, R11.1, R13.1, R14.1
regen-1-1: R3.2, R4.1
regen-1-2: R5.2, R6.1
regen-1-3: R7.2, R8.1
regen-1-4: R9.2, R10.1
regen-1-5: R11.2, R12.1
regen-1-6: R22.2, R23.1
regen-2: Q3.5, Q3.6, Q3.7, Q3.8, Q3.9, R4.2, R6.2, R8.2, R10.2
regen-2-1: Q2.1, R1.2, R2.2
series_mid: Q3.1, Q3.2, Q3.3, Q6.5, Q6.6, Q6.7, Q6.8, Q6.9
thermal_gate: Q1.3, Q6.4, R18.1, R20.2
thermal_ok: Q4.3, R15.1, R19.2, U3.3
threshold: R12.2, R21.1, R23.2, U1.4

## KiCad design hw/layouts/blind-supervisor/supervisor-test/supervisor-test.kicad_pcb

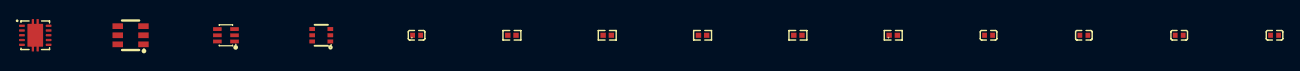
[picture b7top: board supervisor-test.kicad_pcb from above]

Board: 2 copper layers, 14 parts (0 on the bottom side), 10 nets, no tracks yet.

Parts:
C1, C2, C3, C4, C5: C0402
R1, R2, R3, R4, R5: R0402
U1: SC-70-6_L2.0-W1.3-P0.65-LS2.1-BR
U2: SOT-363_L2.0-W1.3-P0.65-LS2.1-BR
U3: SOT-23-6_L2.9-W1.6-P0.95-LS2.8-BR
U4: VSON-10_L3.0-W3.0-P0.50-TL-EP

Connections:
1: R1.2, U2.1
2: R4.2, U2.3
6: U1.6, U2.6, U4.3
CWD: C4.1, U4.2
MR: R5.2, U3.3, U4.8
WDI: U2.4, U4.7
Y: R3.1, U1.4
hv: C1.1, C2.1, C3.1, C5.1, R1.1, R2.1, R4.1, R5.1, U1.5, U2.5, U3.5, U3.6, U4.1, U4.10
lv: C1.2, C2.2, C3.2, C4.2, C5.2, R3.2, U1.2, U1.3, U2.2, U3.2, U4.5, U4.6, U4.11
reset_n: R2.2, U1.1, U3.1
